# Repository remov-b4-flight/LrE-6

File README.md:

Current development was moved to 8-Axis [LrTMAX](https://github.com/remov-b4-flight/LrTMAX) repository.
***
# LrE-6
Adobe Lightroom MIDI Developer Controller project (STM32F072Cx based)  
LrE-6 MIDI controller is formed by embedded hardware board and its firmware.  
It used with [MIDI2LR](https://github.com/rsjaffe/MIDI2LR) software,  
You can control development parameters on RAW photos.  
[YouTube](https://www.youtube.com/watch?v=oeDpP1sG9_Y)  
  
Information related Build,Configure & Use are exists on wiki.  
***
Lightroom is Registerd Trademark of Adobe Corp.

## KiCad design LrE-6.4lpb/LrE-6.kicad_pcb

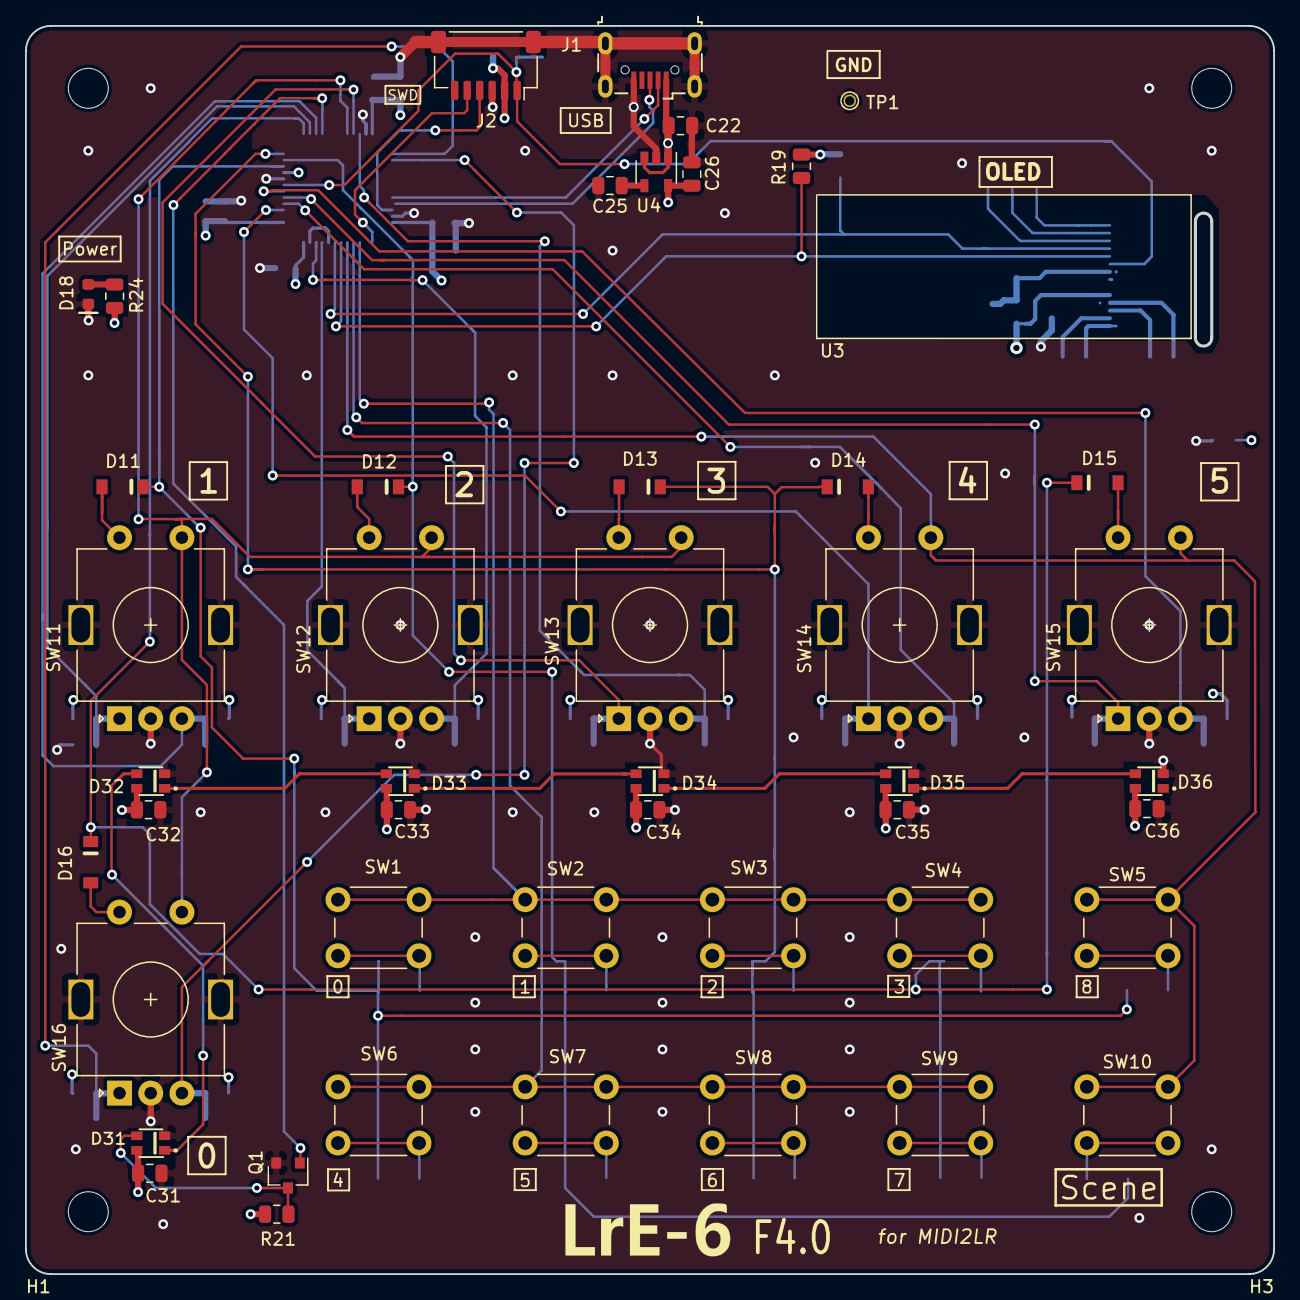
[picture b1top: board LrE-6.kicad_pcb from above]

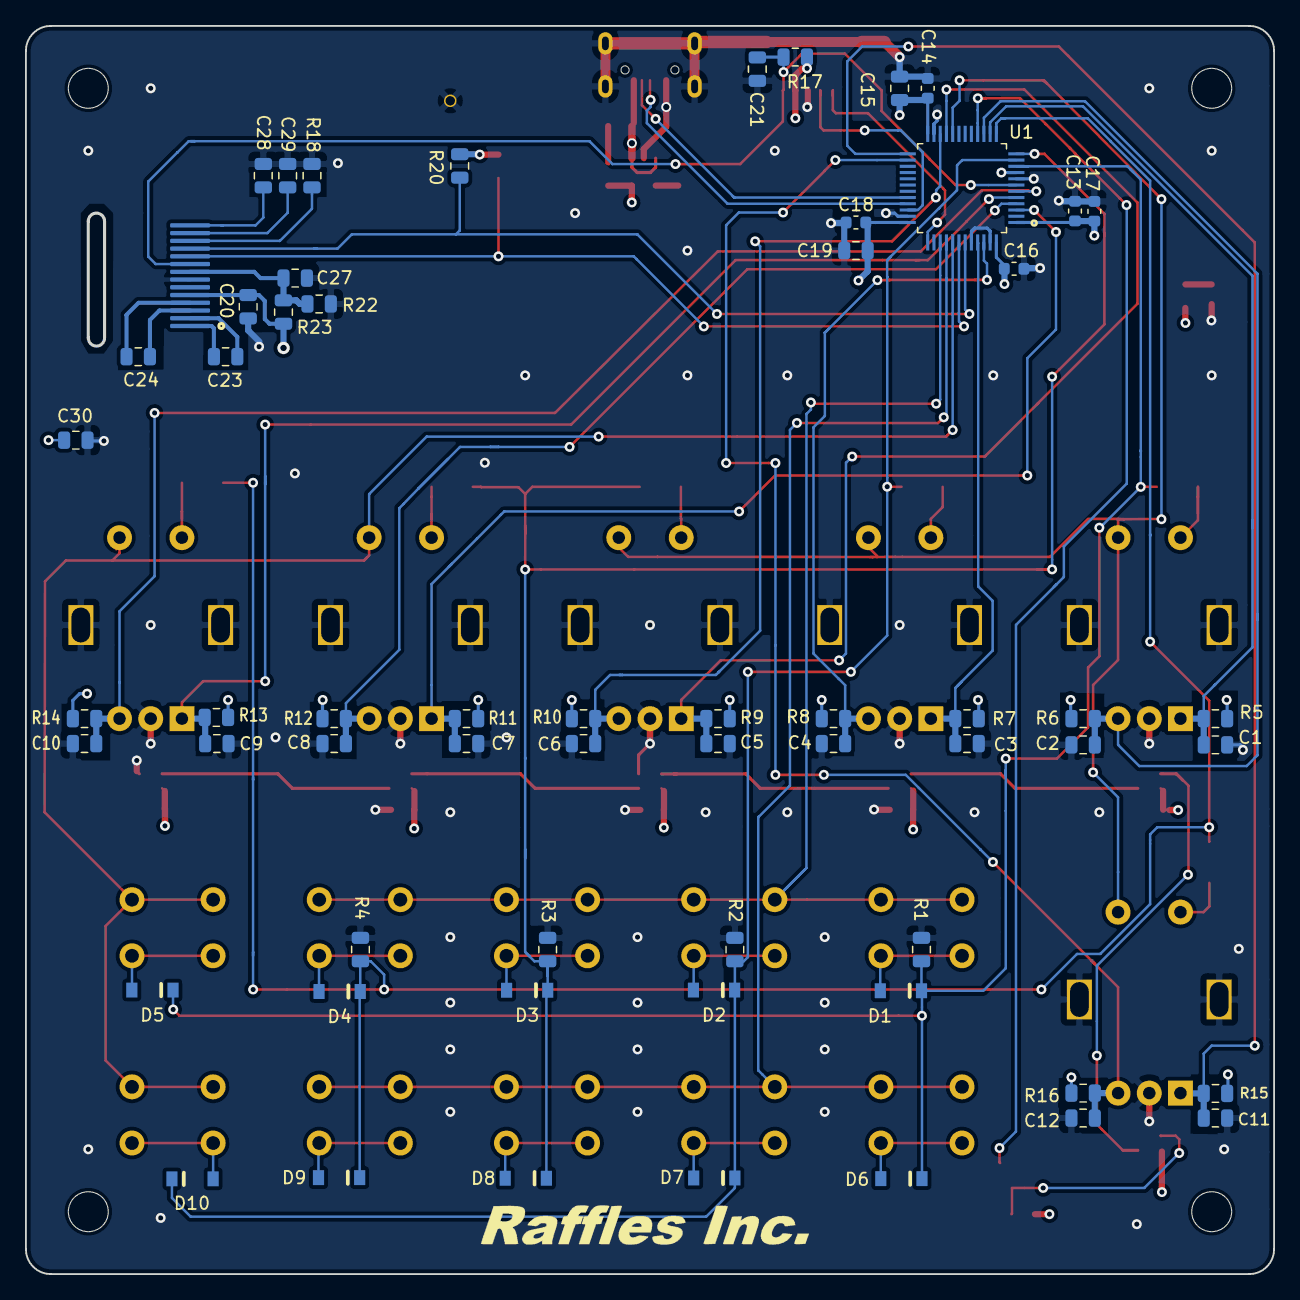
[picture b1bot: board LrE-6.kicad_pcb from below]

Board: 4 copper layers, 99.9 x 99.9 mm, 112 parts (60 on the bottom side), 63 nets.

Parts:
C1, C2, C3, C4, C5, C6, C7, C8, C9, C10, C11, C12, C25: 0.01u; C_0805_2012Metric
C13, C14, C16, C17, C18: 0.1u; C_0603_1608Metric
C15, C19, C28, C29: 4.7u; C_0805_2012Metric
C20, C21, C22, C23, C24, C26, C27: 1u; C_0805_2012Metric
C30, C31, C32, C33, C34, C35, C36: 0.1u; C_0805_2012Metric
D1, D2, D3, D4, D5, D6, D7, D8, D9, D10, D11, D12, D13, D14, D15, D16: 1N4148W; D_SOD-123
D18: LED0603_BL; LED_0603_1608Metric
D31, D32, D33, D34, D35, D36: WS2812B-2020; LED_WS2812B-2020
G001: LrE-6; LOGO
G002: LOGO; Raffles_Inc
H1, H2, H3, H4: MountingHole; MountingHole_3.2mm_M3
J1: USB_B_Micro; USB_Micro-B_MCUBF-09_1
J2: SM06B-SRSS-TB; JST_SH_SM06B-SRSS-TB_1x06-1MP_P1.00mm_Horizontal
Q1: 2N7002; SOT-23
R1, R2, R3, R4, R22, R24: 1K; R_0805_2012Metric
R5, R6, R7, R8, R9, R10, R11, R12, R13, R14, R15, R16, R17, R19, R20, R21: 10K; R_0805_2012Metric
R18: 62; R_0805_2012Metric
R23: 100; R_0805_2012Metric
SW1, SW2, SW3, SW4, SW5, SW6, SW7, SW8, SW9, SW10: Tact_SW_8mm; SW_PUSH_6mm_H9.5mm
SW11, SW12, SW13, SW14, SW15, SW16: EC11_SMD; RotaryEncoder_Alps_EC11E-Switch_Vertical_H20mm
TP1: TestPoint; TestPoint_THTPad_D1.0mm_Drill0.5mm
U1: STM32F072C8Tx; LQFP-48_7x7mm_P0.5mm
U3: SSD1306_OLED_0.91; OLED-9.1
U4: SPX3819M5-L3-3TR; SOT-23-5

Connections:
+3V3: C13.1, C14.2, C15.2, C16.2, C17.2, C18.2, C19.2, C20.1, C26.1, J2.2, R5.1, R6.1, R7.1, R8.1, R9.1, R10.1, R11.1, R12.1, R13.1, R14.1, R15.1, R16.1, R17.1, R19.1, R20.1, R23.1, R24.1, U1.1, U1.9, U1.24, U1.36, U1.48, U3.5, U4.5
/ENC0-A: C11.1, R15.2, SW16.A, U1.25
/ENC0-B: C12.1, R16.2, SW16.B, U1.26
/ENC1-A: C1.1, R5.2, SW11.A, U1.14
/ENC1-B: C2.1, R6.2, SW11.B, U1.15
/ENC2-A: C3.1, R7.2, SW12.A, U1.45
/ENC2-B: C4.1, R8.2, SW12.B, U1.46
/ENC3-A: C5.1, R9.2, SW13.A, U1.21
/ENC3-B: C6.1, R10.2, SW13.B, U1.22
/ENC4-A: C7.1, R11.2, SW14.A, U1.3
/ENC4-B: C8.1, R12.2, SW14.B, U1.4
/ENC5-A: C9.1, R13.2, SW15.A, U1.5
/ENC5-B: C10.1, R14.2, SW15.B, U1.6
/L0: SW1.1, SW2.1, SW3.1, SW4.1, U1.39
/L1: SW6.1, SW7.1, SW8.1, SW9.1, U1.40
/L2: SW5.1, SW10.1, SW14.S1, SW15.S1, U1.41
/L3: SW11.S1, SW12.S1, SW13.S1, SW16.S1, U1.20
/LED1OUT: D31.1, D32.3
/LED2OUT: D32.1, D33.3
/LED3OUT: D33.1, D34.3
/LED4OUT: D34.1, D35.3
/LED5OUT: D35.1, D36.3
/LED_DON: Q1.1, U1.16
/LED_DOUT: D31.3, Q1.3, R21.2
/M0: D1.1, D5.1, D6.1, D11.1, R1.1, U1.10
/M1: D2.1, D7.1, D10.1, D12.1, R2.2, U1.11
/M2: D3.1, D8.1, D13.1, D14.1, R3.1, U1.12
/M3: D4.1, D9.1, D15.1, D16.1, R4.1, U1.13
/NRST: C21.1, J2.1, R17.2, U1.7, U3.9
/SCL: R19.2, U1.42, U3.10
/SDA: R20.2, U1.43, U3.11
/SWCLK: J2.5, U1.37
/SWDIO: J2.4, U1.34
/USB_DM: J1.2, U1.32
/USB_DP: J1.3, U1.33
/VBUS: C22.1, C30.1, C31.1, C32.1, C33.1, C34.1, C35.1, C36.1, D31.4, D32.4, D33.4, D34.4, D35.4, D36.4, J1.1, R21.1, U4.1, U4.3
GND: C1.2, C2.2, C3.2, C4.2, C5.2, C6.2, C7.2, C8.2, C9.2, C10.2, C11.2, C12.2, C13.2, C14.1, C15.1, C16.1, C17.1, C18.1, C19.1, C20.2, C21.2, C22.2, C25.2, C26.2, C27.1, C28.1, C29.1, C30.2, C31.2, C32.2, C33.2, C34.2, C35.2, C36.2, D18.1, D31.2, D32.2, D33.2, D34.2, D35.2, D36.2, J1.5, J1.6, J2.3, J2.MP, Q1.2, R1.2, R2.1, R3.2, R4.2, R18.2, R22.2, SW11.C, SW11.MP, SW12.C, SW12.MP, SW13.C, SW13.MP, SW14.C, SW14.MP, SW15.C, SW15.MP, SW16.C, SW16.MP, TP1.1, U1.8, U1.23, U1.35, U1.44, U1.47, U3.7, U4.2
unnamed: C23.1, U3.2
unnamed: C23.2, U3.1
unnamed: C24.1, U3.4
unnamed: C24.2, U3.3
unnamed: C25.1, U4.4
unnamed: C27.2, R22.1, R23.2, U3.8
unnamed: C28.2, U3.14
unnamed: C29.2, U3.13
unnamed: D1.2, SW1.2
unnamed: D2.2, SW2.2
unnamed: D3.2, SW3.2
unnamed: D4.2, SW4.2
unnamed: D5.2, SW5.2
unnamed: D6.2, SW6.2
unnamed: D7.2, SW7.2
unnamed: D8.2, SW8.2
unnamed: D9.2, SW9.2
unnamed: D10.2, SW10.2
unnamed: D11.2, SW11.S2
unnamed: D12.2, SW12.S2
unnamed: D13.2, SW13.S2
unnamed: D14.2, SW14.S2
unnamed: D15.2, SW15.S2
unnamed: D16.2, SW16.S2
unnamed: D18.2, R24.2
unnamed: R18.1, U3.12

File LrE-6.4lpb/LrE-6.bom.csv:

Reference, Quantity, Value, Footprint, Datasheet
C1 C2 C3 C4 C7 C8 C9 C10 C11 C12 C5 C6 C25 ,13,"0.01u","Capacitor_SMD:C_0805_2012Metric","~"
C13 C16 C17 C18 C14 ,5,"0.1u","Capacitor_SMD:C_0603_1608Metric","~"
C15 C19 C28 C29 ,4,"4.7u","Capacitor_SMD:C_0805_2012Metric","~"
C26 C22 C23 C24 C21 C20 C27 ,7,"1u","Capacitor_SMD:C_0805_2012Metric","~"
C31 C32 C33 C35 C36 C34 C30 ,7,"0.1u","Capacitor_SMD:C_0805_2012Metric","~"
D18 ,1,"LED0603_BL","LED_SMD:LED_0603_1608Metric","~"
D31 D32 D33 D34 D35 D36 ,6,"WS2812B-2020","LrE-6:LED_WS2812B-2020","https://cdn-shop.adafruit.com/product-files/2686/SK6812MINI_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"
D4 D9 D3 D8 D2 D7 D10 D1 D6 D5 D12 D11 D13 D14 D15 D16 ,16,"1N4148W","LrE-6:D_SOD-123","https://www.vishay.com/docs/85748/1n4148w.pdf"
H1 H2 H3 H4 ,4,"MountingHole","MountingHole:MountingHole_3.2mm_M3","~"
J1 ,1,"USB_B_Micro","LrE-6:USB_Micro-B_MCUBF-09_1","~"
J2 ,1,"SM06B-SRSS-TB","Connector_JST:JST_SH_SM06B-SRSS-TB_1x06-1MP_P1.00mm_Horizontal","~"
Q1 ,1,"2N7002","Package_TO_SOT_SMD:SOT-23","https://www.fairchildsemi.com/datasheets/2N/2N7002.pdf"
R18 ,1,"62","Resistor_SMD:R_0805_2012Metric","~"
R19 R20 R6 R5 R8 R7 R10 R9 R12 R11 R14 R13 R16 R15 R17 R21 ,16,"10K","Resistor_SMD:R_0805_2012Metric","~"
R23 ,1,"100","Resistor_SMD:R_0805_2012Metric","~"
R4 R3 R2 R1 R24 R22 ,6,"1K","Resistor_SMD:R_0805_2012Metric","~"
SW1 SW2 SW3 SW4 SW5 SW6 SW7 SW8 SW9 SW10 ,10,"Tact_SW_8mm","Button_Switch_THT:SW_PUSH_6mm_H9.5mm",""
SW11 SW12 SW13 SW14 SW15 SW16 ,6,"EC11_SMD","LrE-6:RotaryEncoder_EC11E-SMD2","~"
TP1 ,1,"TestPoint","TestPoint:TestPoint_THTPad_D1.0mm_Drill0.5mm","~"
U1 ,1,"STM32F072C8Tx","Package_QFP:LQFP-48_7x7mm_P0.5mm","http://www.st.com/st-web-ui/static/active/en/resource/techni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"
U3 ,1,"SSD1306_OLED_0.91","LrE-6:OLED-9.1",""
U4 ,1,"SPX3819M5-L3-3TR","Package_TO_SOT_SMD:SOT-23-5","http://www.st.com/content/ccc/resource/technical/document/da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"

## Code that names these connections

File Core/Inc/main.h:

/* USER CODE BEGIN Header */
/**
  ******************************************************************************
  * @file	main.h
  * @brief	Header for main.c file.
  * 		This file contains the common defines of the application.
  ******************************************************************************
  * @attention
  *
  * <h2><center>&copy; Copyright (c) 2021 STMicroelectronics.
  * All rights reserved.</center></h2>
  *
  * This software component is licensed by ST under Ultimate Liberty license
  * SLA0044, the "License"; You may not use this file except in compliance with
  * the License. You may obtain a copy of the License at:
  *                             www.st.com/SLA0044
  *
  ******************************************************************************
  */
/* USER CODE END Header */

/* Define to prevent recursive inclusion -------------------------------------*/
#ifndef __MAIN_H
#define __MAIN_H

#ifdef __cplusplus
extern "C" {
#endif

/* Includes ------------------------------------------------------------------*/
#include "stm32f0xx_hal.h"

/* Private includes ----------------------------------------------------------*/
/* USER CODE BEGIN Includes */
#define USBD_DEVICE_VER_MAJ	0x00
#define USBD_DEVICE_VER_MIN	0x59
/* USER CODE END Includes */

/* Exported types ------------------------------------------------------------*/
/* USER CODE BEGIN ET */
typedef union keyscan_t {
    uint32_t wd;
    struct ks_bit_t {
		unsigned char n0:4;		//Switch Line0
		unsigned char n1:4;		//Switch Line1
		unsigned char n2:4;		//Switch Line2
		unsigned char n3:4;		//Switch Line3
		unsigned char enc0:2;	//Rotary encoder
		unsigned char enc1:2;	//Rotary encoder
		unsigned char enc2:2;	//Rotary encoder
		unsigned char enc3:2;	//Rotary encoder
		unsigned char enc4:2;	//Rotary encoder
		unsigned char enc5:2;	//Rotary encoder
        unsigned char dummy:4;	//dummy
    } nb;
} KEYSCAN;
/* USER CODE END ET */

/* Exported constants --------------------------------------------------------*/
/* USER CODE BEGIN EC */

/* USER CODE END EC */

/* Exported macro ------------------------------------------------------------*/
/* USER CODE BEGIN EM */

/* USER CODE END EM */

void HAL_TIM_MspPostInit(TIM_HandleTypeDef *htim);

/* Exported functions prototypes ---------------------------------------------*/
void Error_Handler(void);

/* USER CODE BEGIN EFP */

/* USER CODE END EFP */

/* Private defines -----------------------------------------------------------*/
#define Lr_PID 0xA320
#define TIM_PERIOD_24mS 24576
#define TIM_PERIOD_8mS 7999
#define TIM_PERIOD_32mS 32768
#define TIM_PERIOD_125uS 125
#define PWM_HI 38
#define TIM_PRESC_1uS 47
#define Lr_VENDOR "Ruffles Inc."
#define PWM_LO 15
#define Lr_PRODUCT "LrE-6"
#define PWM_PERIOD 59
#define ENC4A_Pin GPIO_PIN_14
#define ENC4A_GPIO_Port GPIOC
#define ENC4A_EXTI_IRQn EXTI4_15_IRQn
#define ENC4B_Pin GPIO_PIN_15
#define ENC4B_GPIO_Port GPIOC
#define ENC4B_EXTI_IRQn EXTI4_15_IRQn
#define ENC5A_Pin GPIO_PIN_0
#define ENC5A_GPIO_Port GPIOF
#define ENC5A_EXTI_IRQn EXTI0_1_IRQn
#define ENC5B_Pin GPIO_PIN_1
#define ENC5B_GPIO_Port GPIOF
#define ENC5B_EXTI_IRQn EXTI0_1_IRQn
#define M0_Pin GPIO_PIN_0
#define M0_GPIO_Port GPIOA
#define M1_Pin GPIO_PIN_1
#define M1_GPIO_Port GPIOA
#define M2_Pin GPIO_PIN_2
#define M2_GPIO_Port GPIOA
#define M3_Pin GPIO_PIN_3
#define M3_GPIO_Port GPIOA
#define ENC1A_Pin GPIO_PIN_4
#define ENC1A_GPIO_Port GPIOA
#define ENC1A_EXTI_IRQn EXTI4_15_IRQn
#define ENC1B_Pin GPIO_PIN_5
#define ENC1B_GPIO_Port GPIOA
#define ENC1B_EXTI_IRQn EXTI4_15_IRQn
#define LED_DON_Pin GPIO_PIN_6
#define LED_DON_GPIO_Port GPIOA
#define L3_Pin GPIO_PIN_2
#define L3_GPIO_Port GPIOB
#define ENC3A_Pin GPIO_PIN_10
#define ENC3A_GPIO_Port GPIOB
#define ENC3A_EXTI_IRQn EXTI4_15_IRQn
#define ENC3B_Pin GPIO_PIN_11
#define ENC3B_GPIO_Port GPIOB
#define ENC3B_EXTI_IRQn EXTI4_15_IRQn
#define ENC0A_Pin GPIO_PIN_12
#define ENC0A_GPIO_Port GPIOB
#define ENC0A_EXTI_IRQn EXTI4_15_IRQn
#define ENC0B_Pin GPIO_PIN_13
#define ENC0B_GPIO_Port GPIOB
#define ENC0B_EXTI_IRQn EXTI4_15_IRQn
#define USB_DM_Pin GPIO_PIN_11
#define USB_DM_GPIO_Port GPIOA
#define USB_DP_Pin GPIO_PIN_12
#define USB_DP_GPIO_Port GPIOA
#define SWDIO_Pin GPIO_PIN_13
#define SWDIO_GPIO_Port GPIOA
#define SWCLK_Pin GPIO_PIN_14
#define SWCLK_GPIO_Port GPIOA
#define L0_Pin GPIO_PIN_3
#define L0_GPIO_Port GPIOB
#define L1_Pin GPIO_PIN_4
#define L1_GPIO_Port GPIOB
#define L2_Pin GPIO_PIN_5
#define L2_GPIO_Port GPIOB
#define SCL_Pin GPIO_PIN_6
#define SCL_GPIO_Port GPIOB
#define SDA_Pin GPIO_PIN_7
#define SDA_GPIO_Port GPIOB
#define ENC2A_Pin GPIO_PIN_8
#define ENC2A_GPIO_Port GPIOB
#define ENC2A_EXTI_IRQn EXTI4_15_IRQn
#define ENC2B_Pin GPIO_PIN_9
#define ENC2B_GPIO_Port GPIOB
#define ENC2B_EXTI_IRQn EXTI4_15_IRQn
/* USER CODE BEGIN Private defines */
#undef	Lr_PID
#undef	Lr_PRODUCT
#define Lr_PID 0xA320
#define Lr_PRODUCT "LrE-6"
#define Lr_VENDOR "Ruffles Inc."

//! Lr**** Hardware definition
#define KEY_COUNT	16
#define	ENC_COUNT	6

//! Lr**** States
enum lr_state_t {
	LR_RESET,        //!< LR_RESET
	LR_USB_NOLINK,   //!< LRE6_USB_NOLINK
	LR_USB_LINKUP,   //!< LR_USB_LINKUP
	LR_USB_LINKED,   //!< LR_USB_LINKED
	LR_USB_LINK_LOST,//!< LR_USB_LINK_LOST
};

//! Key matrix lines
enum {
	L0 = 0,
	L1,
	L2,
	L3
};

//! Scene definition in MIDI
enum lr_scene_t {
	Lr_SCENE0 = 0,
	Lr_SCENE1 = 1,
	Lr_SCENE2 = 2,
	Lr_SCENE3 = 3,
};
#define	SCENE_COUNT		4

//! Encoder definitions
enum lr_enc_t {
	Lr_ENC0 = 0,
	Lr_ENC1,
	Lr_ENC2,
	Lr_ENC3,
	Lr_ENC4,
	Lr_ENC5,
};
//! Define key that designated for scene change.
#define SCENE_BIT			9
#define CC_CH_OFFSET		64
#define CC_CH_PER_SCENE		8
#define NOTES_PER_SCENE		32
//! Key define structure
#define DEFINES_PER_SCENE	( KEY_COUNT + (ENC_COUNT * 2) )

// Screen timer definitions
#define MSG_TIMER_DEFAULT	122		//4Sec (1 tick=32.7ms)
#define MSG_TIMER_UPDATE	31		//1Sec (OLED update in USB not connected)

// LED timer definitions
#define LED_TIM_NORM		21		//500ms (1 tick=24ms)
#define LED_TIM_HALF		11		//250ms
#define LED_TIM_LONG		42		//1Sec
#define LED_TIM_CONNECT		83		//2Sec
//! LED TIM3 definitions
#define LED_TIM_RETRY_WAIT	21		//Transfer period for I2C

//! I2C time definitions
#define I2C_RETRY_WAIT		2		//Transfer period for TIM3 PWM

/* USER CODE END Private defines */

#ifdef __cplusplus
}
#endif

#endif /* __MAIN_H */

/************************ (C) COPYRIGHT STMicroelectronics *****END OF FILE****/

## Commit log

2019-03-22 1st commit
2019-03-25 Add ESP-WROOM-02 TX/RX function
2019-03-26 For Documentation
2019-03-26 Image rename
2019-03-28 Add some WROOM Functionality
2019-04-02 revise PB to R1.11
2019-04-18 Add MIDI2LR layer codes.
2019-06-12 R2.0
    Board Revision 2.0 & firmware working for board 2.0
2019-07-03 elemental functions for R2.0 board.
2019-07-06 switch back to atolic
2019-07-07 adjust key define
2019-07-11 0.02
    Fully functional board revision 2.0(except wifi)
2019-07-21 WROOM passthrouth connection established.
2019-07-24 for WROOM multiple connection mode
2019-08-03 building WiFi connection.
2019-08-13 LrE6 Board R2.01
2019-08-14 modify gitignore
2019-08-14 0.03 final for Board R2.0
2019-08-22 Add wiki photo
2019-08-25 final for R2.00 board
2019-08-25 R2.00 board final
2019-08-26 0.1 for board R2.01 first commit
2019-08-26 0.2 midi brunch first commit
2019-08-26 exclude MIDI code.
2019-08-26 set firmware version 0.20
2019-08-27 0.20 1st MIDI impliment.
2019-08-27 0.10 remove midi codes.
2019-08-27 Add LICENCE And README.md
2019-08-28 exclude WROOM & MIDI code
2019-08-31 Move to MX5.3
2019-08-31 Move to MX5.3 & VID/PID => 0x1209/0xA320
2019-09-11 Back to Atollic + MX5.3 with latest modifications
2019-09-14 Back to Atolic
2019-09-20 0.11-pre1
2019-09-20 0.21-pre
2019-09-20 0.21-pre1
2019-09-21 0.11-pre2 fix for 9.5KQ encoder
2019-09-25 0.11-pre3 restore 'missing key relase'
2019-09-26 0.11-pre4 optimize handling for encoders
2019-09-26 0.21-pre2
2019-09-26 0.11 add to handle 9.5KQ rotary encoder
2019-09-26 0.21-pre4
2019-10-20 0.22-pre1
2019-10-20 0.22-pre2
2019-10-22 0.22-pre3
2019-10-22 0.22-pre4
2019-10-22 0.22-pre5
2019-10-25 0.22
2019-10-28 0.23-pre
2019-10-28 0.23-pre2
2019-10-29 0.23-pre5
2019-10-29 0.23-pre6 moved to STM32CubeIDE
2019-10-30 0.23
2019-10-30 0.23-1
2019-10-31 0.23-2
2019-10-31 0.23-3
2019-11-02 0.24-pre0
2019-11-03 0.24-pre1
    remove usart1,tim16
    add tim2=LCD backlight
2019-11-04 0.24-pre2
2019-11-05 0.24-pre3
2019-11-06 0.24-pre4
2019-11-12 0.24-pre5
2019-11-16 0.25-pre0
2019-11-16 0.25-pre1
2019-11-16 0.25-pre2
2019-11-17 0.25
2019-11-17 0.25-1
2019-11-24 0.25-2
2019-12-07 0.27
    Back to F0_V1.10.0
2019-12-22 0.27-1
    some refactoring.
2019-12-29 0.27-5
2020-01-07 0.27-6
2020-02-02 pb R2.1pre
2020-02-17 0.28-3
2020-02-17 0.28-4
2020-02-18 0.28-5
2020-02-24 0.28-6
    change Rotary Encoder from 9.5KQ to 'symmetry hole' model.
2020-03-02 0.28-7
    F2.2 PCB ordered.
2020-03-04 0.30
    MX Application Structure switched to 'Advanced'
2020-03-05 0.31
    Moved to STM32F0 1.11.0 based.
2020-03-07 0.32
    First SSD1306 OLED implementation.
2020-03-15 0.32
    F2.2 PB first run
2020-03-16 0.32-1
    Fixed SSD1306 Horizontal paging initialize
2020-03-19 0.33
    enables I2C TX DMA
2020-03-24 0.33-1
    modify EC11/9.5KQ structure.
2020-03-26 0.33-2
    add doxygen environment
2020-03-26 0.33-3
    remove un-needed sources for F2.2 board.
2020-03-29 0.33-4
    Add Knob FreeCAD resources
2020-04-04 0.33-5
    F2.8 board
2020-04-04 0.33-6
    add Graphical banner message.
2020-04-05 0.34
    Add rotary encoder knob FreeCAD data
2020-04-06 0.34-1
    modify comments for doxygen
2020-04-07 0.34-2
    C
2020-04-09 0.34-3
    Implement sleep functions.
2020-04-10 0.34-4
    Fix Msg_Timer
2020-04-15 0.34-5
    Delete i2c-lcd.h depend
2020-04-15 0.35
2020-04-16 0.35-1
2020-04-25 0.35-2
    updates doxygen tag.
2020-05-03 0.35-3
    fix for WS2812 LEDs
2020-05-04 0.36
    temporary fix for WS2812 LEDs.
    note: 'stm32f0xx_hal_tim.c' must compile with no optimization.(-O0)
2020-05-16 0.37
    LED axis settings are marged into key definition.
2020-05-16 0.37-1
    Youtube Link was adeed in README.md
2020-05-17 0.37-2
    omit initial SSD1306_Flashscreen()
2020-05-17 0.37-2.1
    fix README.md
2020-05-21 0.37-3
2020-05-23 0.37-4
    some workaround did for OLED issue.
2020-06-04 0.37-5
    change README.md video conents.
2020-06-08 0.37-6
    Fix pb for OLED stability.
2020-06-09 0.37-7
    LrE-6.pb F2.8-1 is ready for order.
2020-06-13 Change Readme photo.
2020-06-13 change readme photo again.
2020-06-13 0.38
    Scene diplay on screen.
2020-06-19 wiki image renaming
2020-09-11 0.39
    Fix for HID mode
2020-09-18 0.41-pre
    moved STM32Cube FW_F0_V1.11.1 & activate TIM7 for cancelling chatter.
2020-09-21 0.42-pre
    Convert EXTI int. -> TIM7 scanning.
2020-09-21 0.42-pre1
    tweak TIM7 ISR
2020-09-21 0.42-pre2
    TIM7 ISR tweak.
2020-09-21 0.42
    As alpha
2020-09-21 0.42-1
    Fix TIM7 ISR again.
2020-09-21 0.42-2
    Key definition fix.
2020-09-23 0.42-3
    add comments.
2020-09-25 0.42-3
    Consider EC11 encoders
2020-10-26 First commit for F3.2PB
2020-10-28 F3.2 add coper por inhibit
2020-10-31 F3.2 commit for order pb
2020-12-04 0.42-4
    Fix typo
2021-01-13 0.43
    Change initial LCD/LED initialize sequence.
2021-02-07 Rename LrE-6.pb F3.2 to F2.8-2
2021-02-25 folk 4-layer pb as F4.0
2021-02-27 F4.0 board order
2021-02-28 0.44pre
    Prepare for F4.0 board.
2021-02-28 0.44-pre2
    moved to STM32Cube FW_F0 V1.11.2
2021-03-06 0.44-pre3
    for F4.0 board, select EC11 encoder as default.
2021-03-10 0.44-pre4
2021-03-11 0.44
    F4.0 board relased.
2021-03-11 0.44-1
    Encoder on F4.0 board determined as 9.5KQ type.
2021-03-12 0.44-2
    eliminate unused codes & optimize Release setting.
2021-03-12 0.44-3
    optimize build setting.
2021-03-15 0.44-4
    Add #pragma GCC optimize ("O0") HAL_TIM_stm32f0_tim_PWM_DMA_Start /
    Stop.
2021-03-15 Revert "0.44-3"
    This reverts commit c8f7220bb2b73d2015e403d7bb75d4c95cb9c808.
2021-04-09 0.45
    Change rotary encoder de-bouncer capacitor value.
2021-04-09 0.45-1
    rename LrE-6.pb to LrE-6.2lpb
2021-04-09 0.45-2
2021-04-12 0.45-3
    only documentation
2021-04-17 0.45-4
    correct internal state about Scene Key,r emove dead code, correct typos.
2021-06-06 0.45-5
    reflect LrTMAX's edit.
2021-06-07 0.45-6
    Fix some key defines.
2021-06-07 0.46
    Add Error_Handler() to USB MIDI initialize.
2021-06-11 0.46-1
    key_define.c adjust.
2021-06-20 0.46-1
    adjust PWM pulse width for LED. to meet LED spec.
2021-06-26 0.46-2
    (Again) adjusst PWM LED pulse width to meet WS2812C-2020 spec.
2021-07-07 0.47
    backport from LrMAX coding and
    Clean up LrE-6.2lpb old resources.
2021-07-07 0.47-1
    some clean up.
2021-07-08 0.47-2
    fix current USB descriptor.
2021-10-22 0.49
    Back to 0.47-2 and apply 0.48(except GPIO/TIM3ch1 LEDs control).
2021-10-22 0.49-1
    Stop ADC.
2021-10-22 0.49-2
    Fix build setting
2022-02-08 0.58-pre00
    MX generated.
2022-02-10 0.58-pre03
    compiled without errors
2022-02-10 0.58-pre05
2022-02-10 0.58-pre06
2022-02-11 0.58-pre07
2022-02-11 0.58-pre08
2022-02-12 0.58-pre09
    Fixed encoder axis assignment.
2022-02-12 0.58
    backport from LrTMAX 0.58
2022-02-12 0.58-1
    fix connection banner
2022-02-23 0.59
    Backported from LrTMAX 0.59
